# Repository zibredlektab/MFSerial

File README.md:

# MFSerial
Microforce Analog to Preston Serial converter

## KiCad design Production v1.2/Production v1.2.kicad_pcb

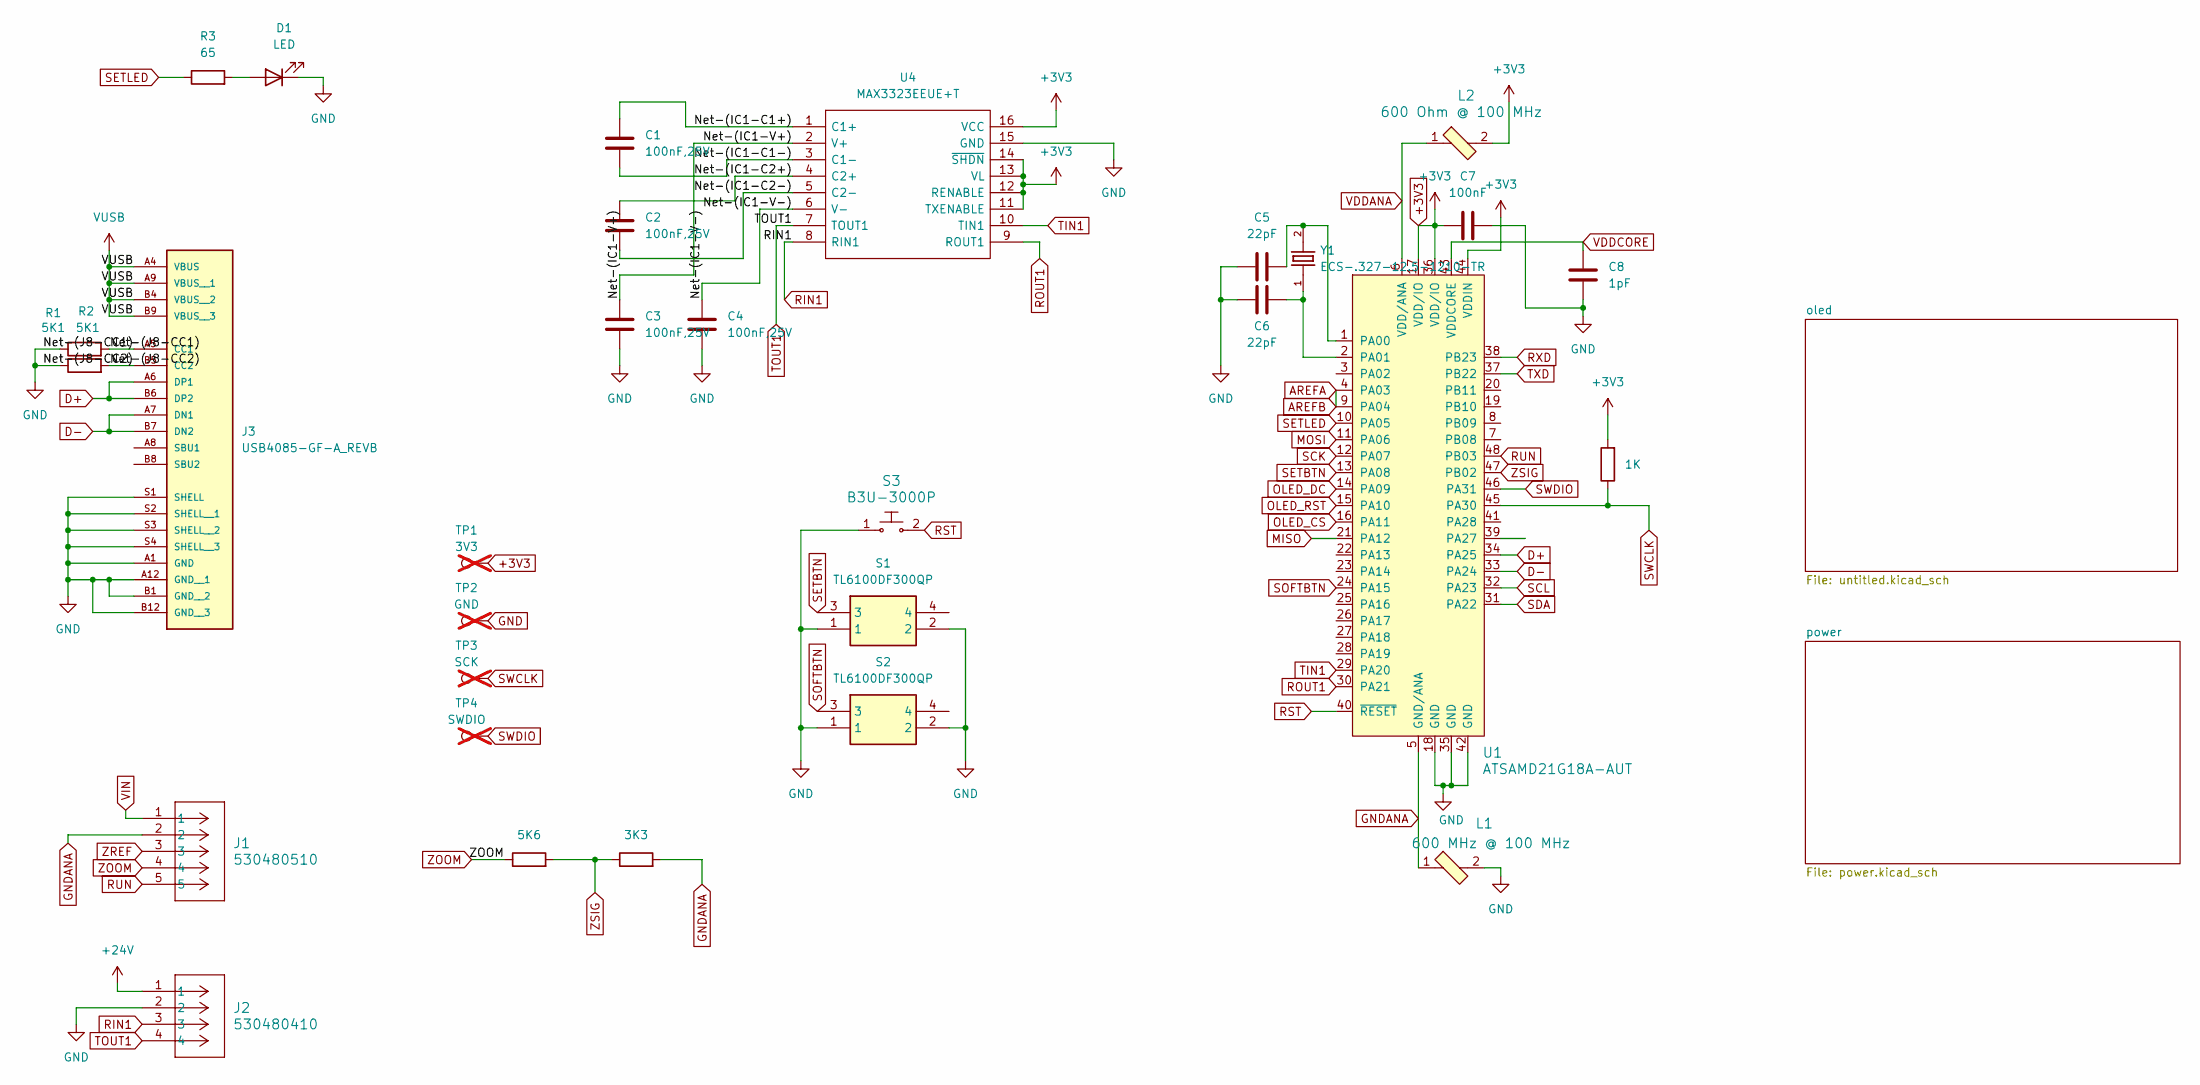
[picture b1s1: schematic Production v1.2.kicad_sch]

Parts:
C1, C2, C3, C4: 100nF,25V; C_0402_1005Metric; Part Number CL05B104KA5NNNC
C5, C6: 22pF; C_0402_1005Metric; Part Number CL05C220JB51PNC
C7: 100nF; C_0402_1005Metric; Part Number CL05B104KA5NNNC
C8: 1pF; C_0402_1005Metric; Part Number CL05C010CB5NNNC
D1: LED; LED_0805_2012Metric; Part Number B1701URO-20D000114U1930
J1: 530480510; Molex_PicoBlade_53048-0510_1x05_P1.25mm_Horizontal; Part Number 530480510
J2: 530480410; Molex_PicoBlade_53048-0410_1x04_P1.25mm_Horizontal; Part Number 530480410
J3: USB4085-GF-A_REVB; CONN16_USB4085-GF-A_GCT; Part Number USB4085-GF-A
L1: 600 MHz @ 100 MHz; 0603; Part Number 74269262601
L2: 600 Ohm @ 100 MHz; 0603; Part Number 74269262601
R1, R2: 5K1; R_0201_0603Metric; Part Number ERJ-1GNF5101C
R3: 65; R_0201_0603Metric; Part Number ERJ-1GNF64R9C
R4: 5K6; R_0402_1005Metric; Part Number ERA-2VRW5601X
R5: 3K3; R_0402_1005Metric; Part Number ERA-2VRW3301X
R6: 1K; R_0201_0603Metric; Part Number RC0201FR-071KL
S1, S2: TL6100DF300QP; TL6100DF160QP; Part Number TL6100DF300QP
S3: B3U-3000P; SW_SPST_B3U-3000P; Part Number B3U-3000P
TP1: 3V3; TestPoint_Pad_1.0x1.0mm; not fitted
TP2: GND; TestPoint_Pad_1.0x1.0mm; not fitted
TP3: SCK; TestPoint_Pad_1.0x1.0mm; not fitted
TP4: SWDIO; TestPoint_Pad_1.0x1.0mm; not fitted
U1: ATSAMD21G18A-AUT; TQFP-48_7x7mm_P0.5mm; Part Number ATSAMD21G18A-AUT
U4: MAX3323EEUE+T; TSSOP-16_4.4x5mm_P0.65mm; Part Number MAX3323EEUE+T
Y1: ECS-.327-12.5-1210-TR; XTAL_ECS-.327-12.5-1210-TR; Part Number ECS-.327-12.5-1210-TR

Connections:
+3V3: C7.1, L2.2, R6.2, TP1.1, U1.17 (VDD/IO), U1.36 (VDD/IO), U1.44 (VDDIN), U4.11 (TXENABLE), U4.12 (RENABLE), U4.13 (VL), U4.14 (~SHDN), U4.16 (VCC); also elsewhere on the board
+24V: J2.1; also elsewhere on the board
/Net-(IC1-C1+): C1.1, U4.1 (C1+)
/Net-(IC1-C1-): C1.2, U4.3 (C1-)
/Net-(IC1-C2+): C2.1, U4.4 (C2+)
/Net-(IC1-C2-): C2.2, U4.5 (C2-)
/Net-(IC1-V+): C3.1, U4.2 (V+)
/Net-(IC1-V-): C4.1, U4.6 (V-)
/Net-(J8-CC1): J3.A5 (CC1), R1.2
/Net-(J8-CC2): J3.B5 (CC2), R2.2
AREFA: U1.4 (PA03), U1.9 (PA04); also elsewhere on the board
D+: J3.A6 (DP1), J3.B6 (DP2), U1.34 (PA25)
D-: J3.A7 (DN1), J3.B7 (DN2), U1.33 (PA24)
GND: C3.2, C4.2, C5.1, C6.1, C7.2, C8.2, D1.1 (K), J2.2, J3.A1 (GND), J3.A12 (GND__1), J3.B1 (GND__2), J3.B12 (GND__3), J3.S1 (SHELL), J3.S2 (SHELL__1), J3.S3 (SHELL__2), J3.S4 (SHELL__3), L1.2, R1.1, R2.1, S1.1, S1.2, S2.1, S2.2, S3.1, TP2.1, U1.18 (GND), U1.35 (GND), U1.42 (GND), U4.15 (GND); also elsewhere on the board
GNDANA: J1.2, L1.1, R5.2, U1.5 (GND/ANA); also elsewhere on the board
MISO: U1.21 (PA12)
MOSI: U1.11 (PA06); also elsewhere on the board
unnamed: D1.2 (A), R3.2
unnamed: C5.2, U1.1 (PA00), Y1.2
unnamed: C6.2, U1.2 (PA01), Y1.1
OLED_CS: U1.16 (PA11); also elsewhere on the board
OLED_DC: U1.14 (PA09); also elsewhere on the board
OLED_RST: U1.15 (PA10); also elsewhere on the board
RIN1: J2.3, U4.8 (RIN1)
ROUT1: U1.30 (PA21), U4.9 (ROUT1)
RST: S3.2, U1.40 (~RESET)
RUN: J1.5, U1.48 (PB03)
RXD: U1.38 (PB23)
SCK: U1.12 (PA07); also elsewhere on the board
SCL: U1.32 (PA23)
SDA: U1.31 (PA22)
SETBTN: S1.3, U1.13 (PA08)
SETLED: R3.1, U1.10 (PA05)
SOFTBTN: S2.3, U1.24 (PA15)
SWCLK: R6.1, TP3.1, U1.45 (PA30)
SWDIO: TP4.1, U1.46 (PA31)
TIN1: U1.29 (PA20), U4.10 (TIN1)
TOUT1: J2.4, U4.7 (TOUT1)
TXD: U1.37 (PB22)
VDDANA: L2.1, U1.6 (VDD/ANA); also elsewhere on the board
VDDCORE: C8.1, U1.43 (VDDCORE)
VIN: J1.1; also elsewhere on the board
VUSB: J3.A4 (VBUS), J3.A9 (VBUS__1), J3.B4 (VBUS__2), J3.B9 (VBUS__3); also elsewhere on the board
ZOOM: J1.4, R4.1
ZREF: J1.3; also elsewhere on the board
ZSIG: R4.2, R5.1, U1.47 (PB02)

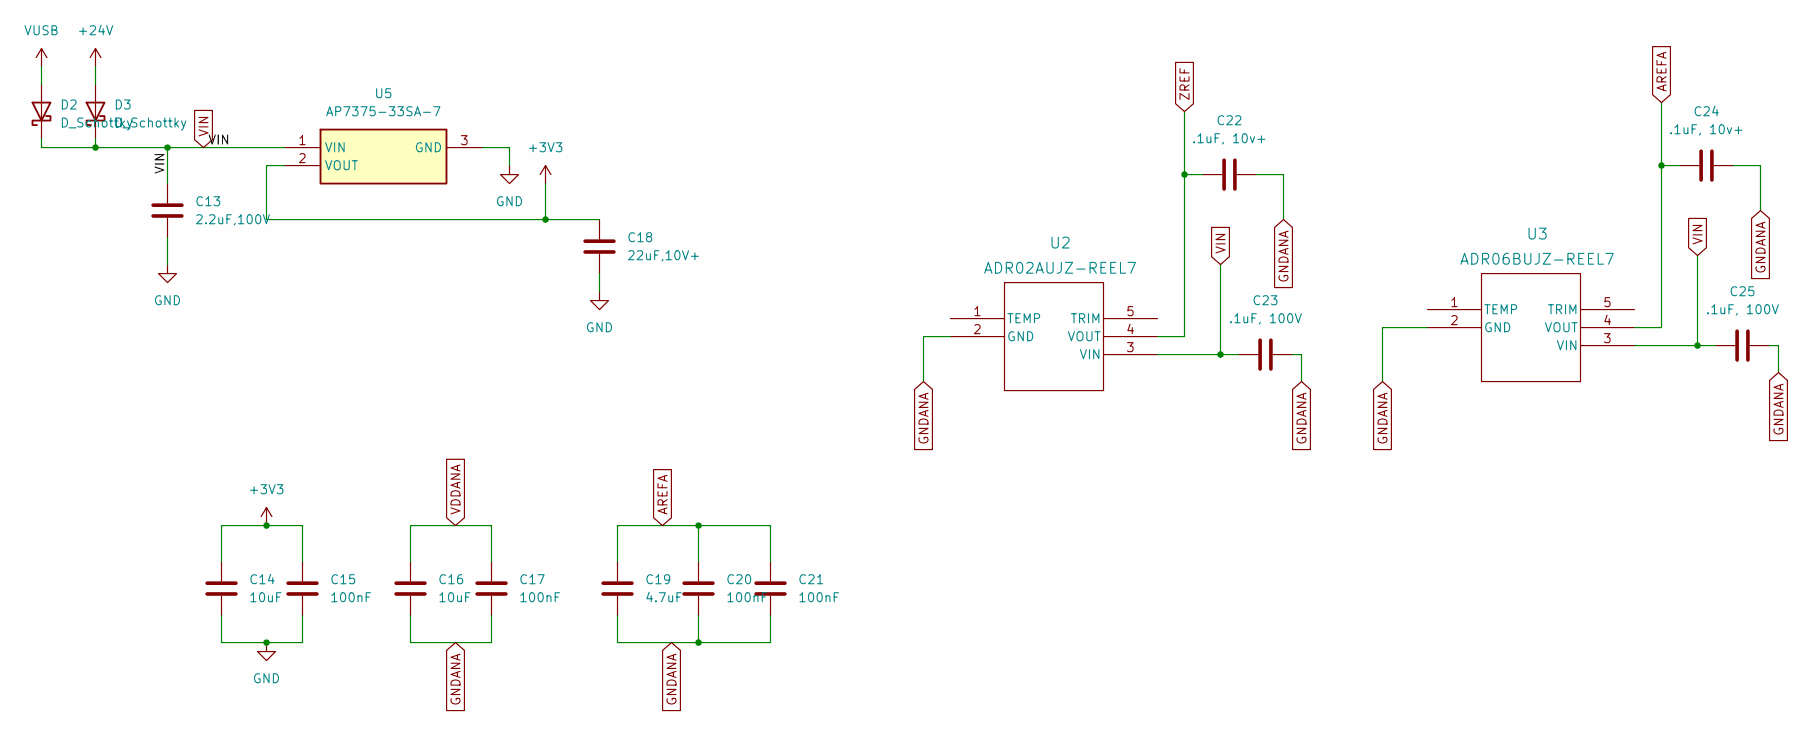
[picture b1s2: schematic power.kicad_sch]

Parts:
C13: 2.2uF,100V; C_0805_2012Metric; Part Number C2012X7R2A225K125AC
C14, C16: 10uF; C_0402_1005Metric; Part Number GRM155R61A106ME11D
C15, C17, C20, C21: 100nF; C_0402_1005Metric; Part Number CL05B104KA5NNNC
C18: 22uF,10V+; C_0402_1005Metric; Part Number GRM158R61A226ME15D
C19: 4.7uF; C_0402_1005Metric; Part Number CL05A475MP5NRNC
C22, C24: .1uF, 10v+; C_0402_1005Metric; Part Number CL05B104KP5NNNC
C23, C25: .1uF, 100V; C_0805_2012Metric; Part Number CL21B104KCFNNNE
D2, D3: D_Schottky; D_1206_3216Metric; Part Number SD1206S100S1R0
U2: ADR02AUJZ-REEL7; TSOT-23-5; Part Number ADR02AUJZ-REEL7
U3: ADR06BUJZ-REEL7; TSOT-23-5; Part Number ADR06BUJZ-REEL7
U5: AP7375-33SA-7; SOT96P240X110-3N; Part Number AP7375-33SA-7

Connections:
+3V3: C14.1, C15.1, C18.2, U5.2 (VOUT); also elsewhere on the board
+24V: D3.2 (A); also elsewhere on the board
AREFA: C19.1, C20.1, C21.1, C24.2, U3.4 (VOUT); also elsewhere on the board
GND: C13.1, C14.2, C15.2, C18.1, U5.3 (GND); also elsewhere on the board
GNDANA: C16.2, C17.2, C19.2, C20.2, C21.2, C22.1, C23.1, C24.1, C25.1, U2.2 (GND), U3.2 (GND); also elsewhere on the board
VDDANA: C16.1, C17.1; also elsewhere on the board
VIN: C13.2, C23.2, C25.2, D2.1 (K), D3.1 (K), U2.3 (VIN), U3.3 (VIN), U5.1 (VIN); also elsewhere on the board
VUSB: D2.2 (A); also elsewhere on the board
ZREF: C22.2, U2.4 (VOUT); also elsewhere on the board

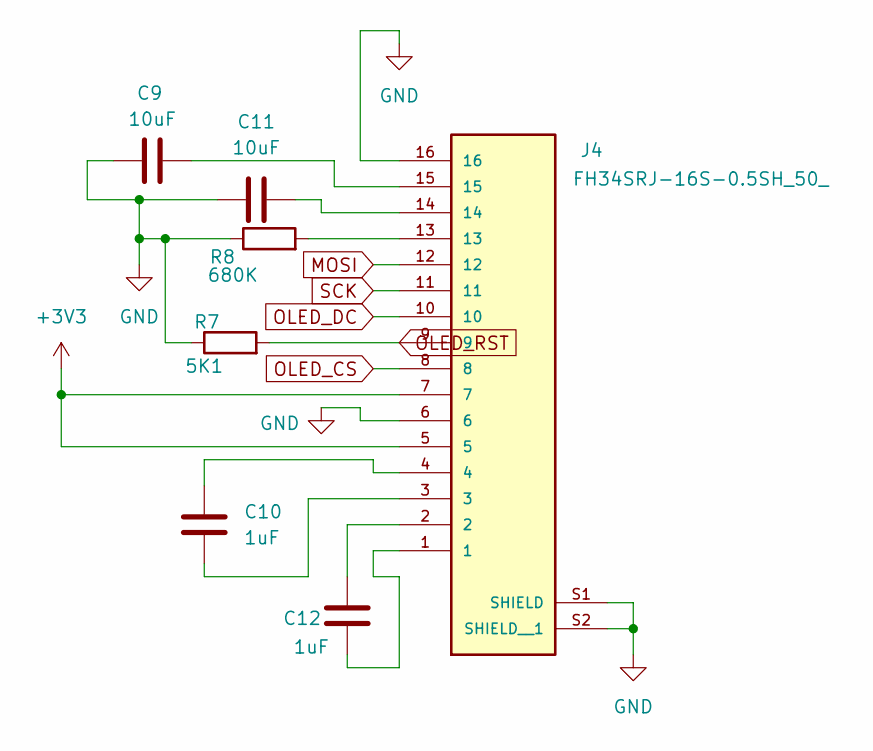
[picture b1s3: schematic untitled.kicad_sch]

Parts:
C9, C11: 10uF; C_0603_1608Metric; Part Number CL10A106KQ8NNNL
C10, C12: 1uF; C_0603_1608Metric; Part Number CL10B105KP8NNNC
J4: FH34SRJ-16S-0.5SH_50_; HRS_FH34SRJ-16S-0.5SH_50_; Part Number FH34SRJ-16S-0.5SH(50)
R7: 5K1; R_0201_0603Metric; Part Number ERJ-1GNF5101C
R8: 680K; R_0201_0603Metric; Part Number ERJ-1GNF6803C

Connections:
+3V3: J4.5, J4.7; also elsewhere on the board
GND: C9.1, C11.2, J4.6, J4.16, J4.S1 (SHIELD), J4.S2 (SHIELD__1), R7.1, R8.1; also elsewhere on the board
MOSI: J4.12; also elsewhere on the board
unnamed: C9.2, J4.15
unnamed: C10.1, J4.3
unnamed: C10.2, J4.4
unnamed: C11.1, J4.14
unnamed: C12.1, J4.1
unnamed: C12.2, J4.2
unnamed: J4.13, R8.2
OLED_CS: J4.8; also elsewhere on the board
OLED_DC: J4.10; also elsewhere on the board
OLED_RST: J4.9, R7.2; also elsewhere on the board
SCK: J4.11; also elsewhere on the board

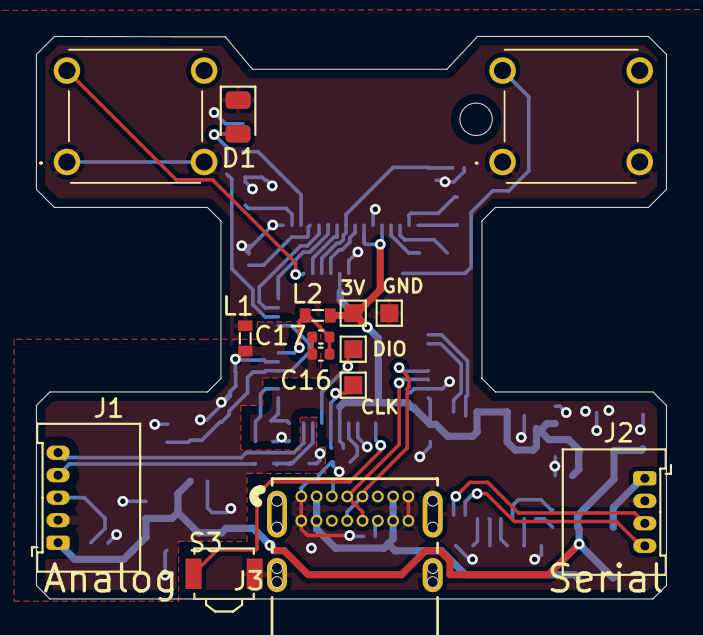
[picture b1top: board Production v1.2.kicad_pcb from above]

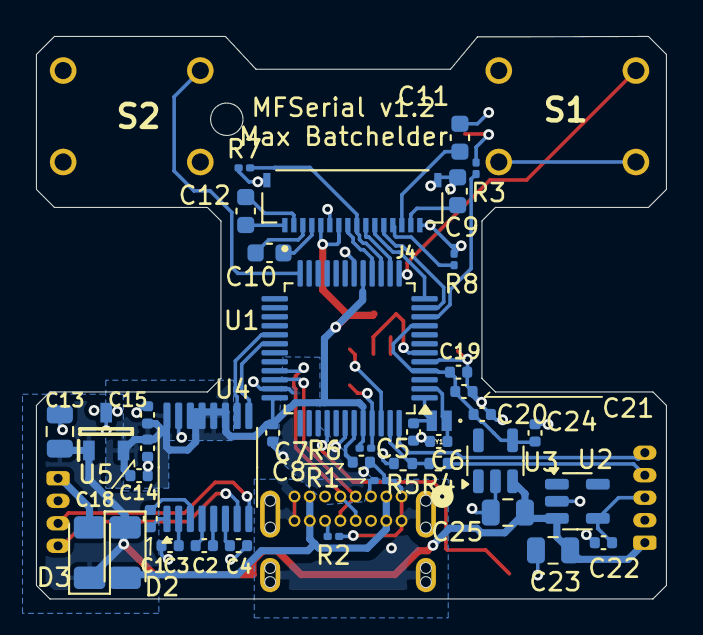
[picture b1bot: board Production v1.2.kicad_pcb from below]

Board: 2 copper layers, 35.0 x 31.2 mm, 55 parts (40 on the bottom side), 48 nets.

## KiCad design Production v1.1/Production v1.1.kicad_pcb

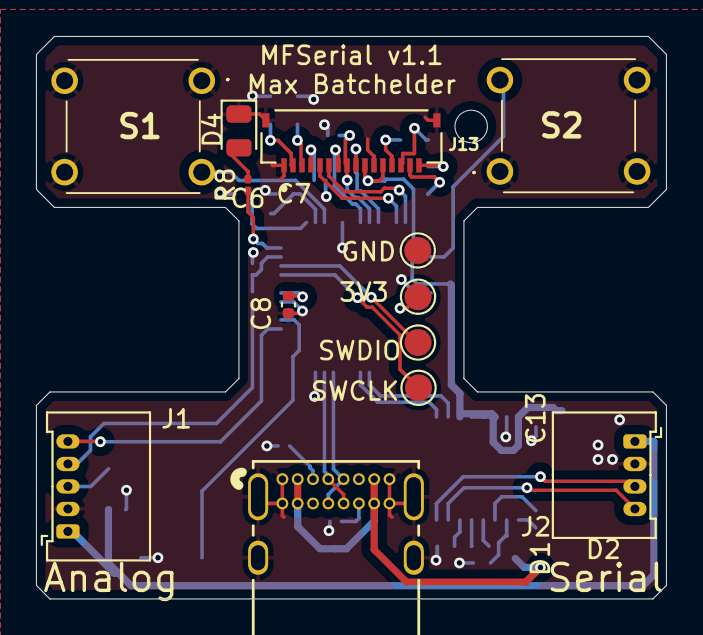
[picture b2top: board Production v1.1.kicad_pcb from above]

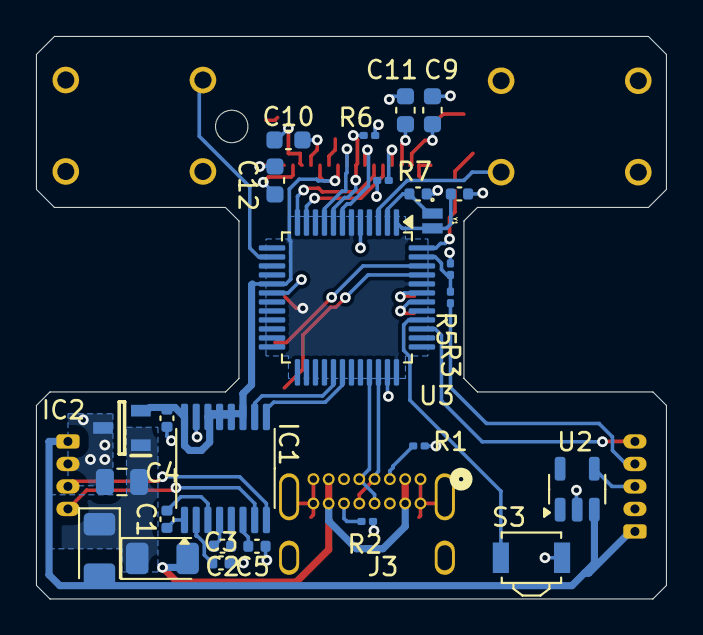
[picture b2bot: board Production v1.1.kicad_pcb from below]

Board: 2 copper layers, 35.0 x 31.2 mm, 39 parts (26 on the bottom side), 45 nets.

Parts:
3V3: TestPoint_Pad_D1.5mm
C1, C2, C3, C5: 100nF,24V+; C_0402_1005Metric
C4: 2.2uF,100V; C_0805_2012Metric
C6, C7: 22pF; C_0402_1005Metric
C8: 1pF; C_0402_1005Metric
C9, C11: 10uF; C_0603_1608Metric
C10, C12: 1uF; C_0603_1608Metric
C13: 22uF,10V+; C_0402_1005Metric
D1, D2: D_Schottky; D_1206_3216Metric
D4: LED; LED_0805_2012Metric
GND: TestPoint_Pad_D1.5mm
IC1: MAX3323EEUE+T; TSSOP-16_4.4x5mm_P0.65mm
IC2: AP7375-33SA-7; SOT96P240X110-3N
J1: 530480510; Molex_PicoBlade_53048-0510_1x05_P1.25mm_Horizontal
J2: 530480410; Molex_PicoBlade_53048-0410_1x04_P1.25mm_Horizontal
J3: USB4085-GF-A_REVB; CONN16_USB4085-GF-A_GCT
J13: FH34SRJ-16S-0.5SH_50_; HRS_FH34SRJ-16S-0.5SH_50_
R1, R2, R6: 5K1; R_0201_0603Metric
R3: 4K7; R_0201_0603Metric
R5: 3K3; R_0201_0603Metric
R7: 680K; R_0201_0603Metric
R8: 65; R_0201_0603Metric
S1, S2: TL6100DF300QP; TL6100DF160QP
S3: B3U-3000P; SW_SPST_B3U-3000P
SWCLK: TestPoint_Pad_D1.5mm
SWDIO: TestPoint_Pad_D1.5mm
U2: ADR02AUJZ-REEL7; TSOT-23-5
U3: ATSAMD21G18A-AUT; TQFP-48_7x7mm_P0.5mm
Y1: ECS-.327-12.5-1210-TR; XTAL_ECS-.327-12.5-1210-TR

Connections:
+3V3: 3V3.3, C13.2, IC1.11 (TXENABLE), IC1.12 (RENABLE), IC1.13 (VL), IC1.14 (~SHDN), IC1.16 (VCC), IC2.2 (VOUT), J13.10, J13.12, U3.6 (VDD/ANA), U3.17 (VDD/IO), U3.36 (VDD/IO), U3.44 (VDDIN)
+24V: D2.2 (A), J1.1, J2.1, U2.3 (VIN)
/Net-(IC1-C1+): C1.1, IC1.1 (C1+)
/Net-(IC1-C1-): C1.2, IC1.3 (C1-)
/Net-(IC1-C2+): C2.1, IC1.4 (C2+)
/Net-(IC1-C2-): C2.2, IC1.5 (C2-)
/Net-(IC1-V+): C3.1, IC1.2 (V+)
/Net-(IC1-V-): C5.1, IC1.6 (V-)
/Net-(J8-CC1): J3.A5 (CC1), R1.2
/Net-(J8-CC2): J3.B5 (CC2), R2.2
D+: J3.A6 (DP1), J3.B6 (DP2), U3.34 (PA25)
D-: J3.A7 (DN1), J3.B7 (DN2), U3.33 (PA24)
GND: C3.2, C4.1, C5.2, C6.1, C7.1, C8.2, C9.1, C11.2, C13.1, D4.1 (K), GND.4, IC1.15 (GND), IC2.3 (GND), J1.2, J2.2, J3.A1 (GND), J3.A12 (GND__1), J3.B1 (GND__2), J3.B12 (GND__3), J3.S1 (SHELL), J3.S2 (SHELL__1), J3.S3 (SHELL__2), J3.S4 (SHELL__3), J13.1, J13.11, J13.S1 (SHIELD), J13.S2 (SHIELD__1), R1.1, R2.1, R5.2, R6.1, R7.1, S1.1, S1.2, S1.4, S2.1, S2.2, S2.4, S3.1, U2.2 (GND), U3.5 (GND/ANA), U3.18 (GND), U3.35 (GND), U3.42 (GND)
MOSI: J13.5, U3.11 (PA06)
unnamed: C9.2, J13.2
unnamed: C10.1, J13.14
unnamed: C10.2, J13.13
unnamed: C11.1, J13.3
unnamed: C12.1, J13.16
unnamed: C12.2, J13.15
unnamed: D4.2 (A), R8.2
unnamed: J13.4, R7.2
unnamed: C6.2, U3.1 (PA00), Y1.2
unnamed: C7.2, U3.2 (PA01), Y1.1
unnamed: C8.1, U3.43 (VDDCORE)
OLED_CS: J13.9, U3.9 (PA04)
OLED_DC: J13.7, U3.7 (PB08)
OLED_RST: J13.8, R6.2, U3.8 (PB09)
RIN1: IC1.8 (RIN1), J2.3
ROUT1: IC1.9 (ROUT1), U3.30 (PA21)
RST: S3.2, U3.40 (~RESET)
RUN: J1.5, U3.39 (PA27)
SCK: J13.6, U3.12 (PA07)
SETBTN: S1.3, U3.3 (PA02)
SETLED: R8.1, U3.48 (PB03)
SOFTBTN: S2.3, U3.14 (PA09)
SWCLK: SWCLK.1, U3.45 (PA30)
SWDIO: SWDIO.3, U3.46 (PA31)
TIN1: IC1.10 (TIN1), U3.29 (PA20)
TOUT1: IC1.7 (TOUT1), J2.4
VIN: C4.2, D1.1 (K), D2.1 (K), IC2.1 (VIN)
VUSB: D1.2 (A), J3.A4 (VBUS), J3.A9 (VBUS__1), J3.B4 (VBUS__2), J3.B9 (VBUS__3)
ZOOM: J1.4, R3.1
ZREF: J1.3, U2.4 (VOUT)
ZSIG: R3.2, R5.1, U3.47 (PB02)

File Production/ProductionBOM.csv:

"Id";"Designator";"Footprint";"Quantity";"Designation";"Supplier and ref";
1;"C8";"C_0504_1310Metric";1;"1pF";;;
2;"D1,D2";"D_1206_3216Metric";2;"D_Schottky";;;
3;"C10,C12";"C_0504_1310Metric";2;"1uF";;;
4;"J1";"Molex_PicoBlade_53048-0510_1x05_P1.25mm_Horizontal";1;"530480510";;;
5;"C7,C6";"C_0504_1310Metric";2;"22pF";;;
6;"J3";"CONN16_USB4085-GF-A_GCT";1;"USB4085-GF-A_REVB";;;
7;"R1,R6,R2";"R_0603_1608Metric";3;"5K1";;;
8;"R8";"R_0603_1608Metric";1;"65";;;
9;"C5,C1,C3,C2";"C_0504_1310Metric";4;"100nF,24V+";;;
10;"U1";"TO-252-3_TabPin2";1;"BD33FC0FP-E2";;;
11;"SOFT1,SET1";"TS016673BK160D";2;"TS01-66-73-BK-160-D";;;
12;"J2";"Molex_PicoBlade_53048-0410_1x04_P1.25mm_Horizontal";1;"530480410";;;
13;"R7";"R_0603_1608Metric";1;"680K";;;
14;"IC1";"TSSOP-16_4.4x5mm_P0.65mm";1;"MAX3323EEPE+";;;
15;"R3";"R_0603_1608Metric";1;"4K7";;;
16;"J13";"HRS_FH34SRJ-16S-0.5SH_50_";1;"FH34SRJ-16S-0.5SH_50_";;;
17;"U3";"TQFP-48_7x7mm_P0.5mm";1;"ATSAMD21G18A-AUT";;;
18;"C11,C9";"C_0504_1310Metric";2;"10uF";;;
19;"U2";"TSOT-23-5";1;"ADR02AUJZ-REEL7";;;
20;"C13,C4";"C_0504_1310Metric";2;"20uF,60V+";;;
21;"Y1";"Crystal_SMD_3215-2Pin_3.2x1.5mm";1;"32.768, 12.5pF";;;
22;"D4";"LED_0805_2012Metric";1;"LED";;;
23;"R5";"R_0603_1608Metric";1;"3K3";;;
24;"RESET1";"SW_SPST_B3U-3000P";1;"B3U-1000P";;;

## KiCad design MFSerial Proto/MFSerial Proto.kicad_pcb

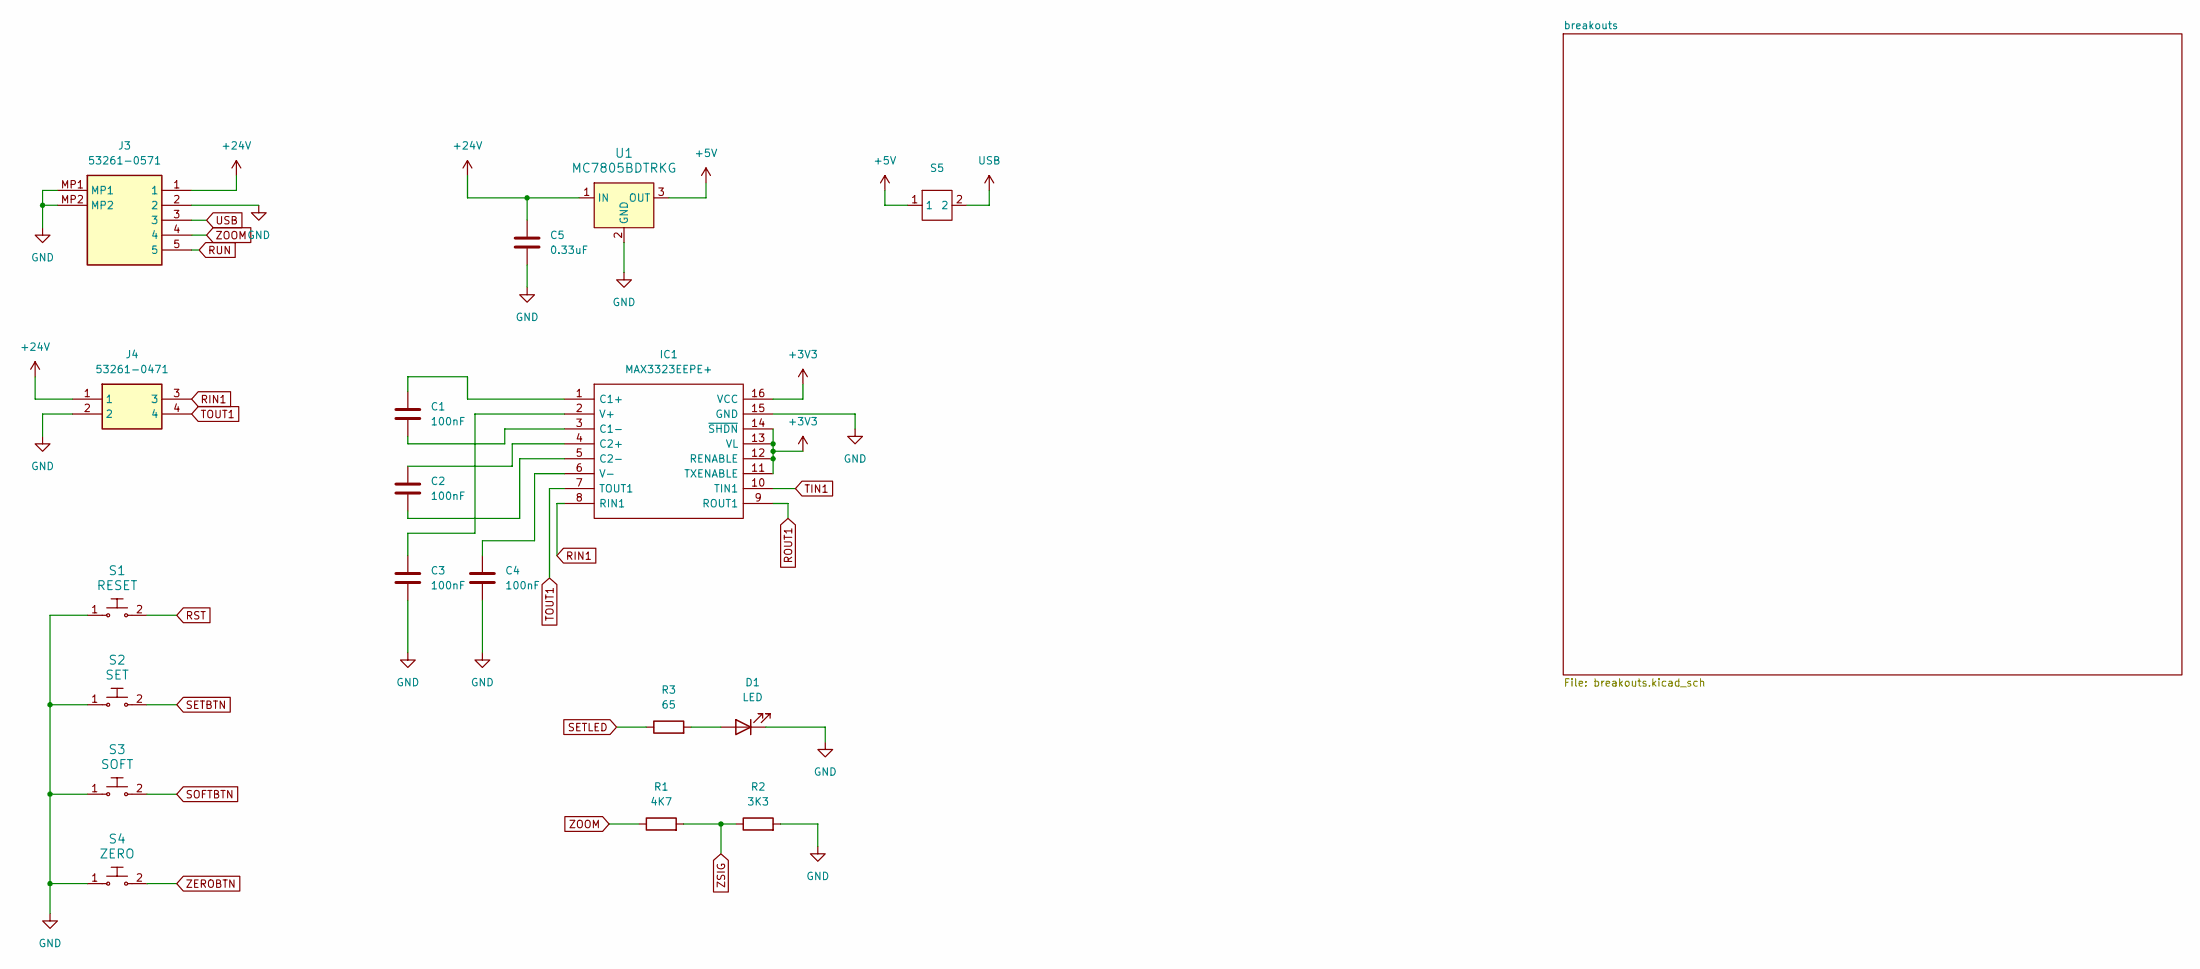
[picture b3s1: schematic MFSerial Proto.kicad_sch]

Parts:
C1, C2, C3, C4: 100nF; C_1812_4532Metric_Pad1.57x3.40mm_HandSolder
C5: 0.33uF; C_1812_4532Metric_Pad1.57x3.40mm_HandSolder
D1: LED; LED_5mm_Radial
IC1: MAX3323EEPE+; DIP794W56P254L1918H457Q16N; Mouser Part Number 700-MAX3323EEPE
J3: 53261-0571; 532610571TR250; Mouser Part Number 538-53261-0571
J4: 53261-0471; Mouser Part Number 538-53261-0471
R1: 4K7; R_1206_3216Metric_Pad1.30x1.75mm_HandSolder
R2: 3K3; R_1206_3216Metric_Pad1.30x1.75mm_HandSolder
R3: 65; R_1206_3216Metric_Pad1.30x1.75mm_HandSolder
S1: RESET; Switch_Tactile_SMD_B3U-1000P; MPN B3U-1000P
S2: SET; Switch_Tactile_SMD_B3U-1000P; MPN B3U-1000P
S3: SOFT; Switch_Tactile_SMD_B3U-1000P; MPN B3U-1000P
S4: ZERO; Switch_Tactile_SMD_B3U-1000P; MPN B3U-1000P
S5: DS04-254-1L-01
U1: MC7805BDTRKG; TO-220-3; MPN MC7805BDTRKG

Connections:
+3V3: IC1.11 (TXENABLE), IC1.12 (RENABLE), IC1.13 (VL), IC1.14 (~SHDN), IC1.16 (VCC); also elsewhere on the board
+5V: S5.1, U1.3 (OUT)
+24V: C5.2, J3.1, J4.1, U1.1 (IN); also elsewhere on the board
GND: C3.2, C4.2, C5.1, D1.1 (K), IC1.15 (GND), J3.2, J3.MP1, J3.MP2, J4.2, R2.2, S1.1, S2.1, S3.1, S4.1, U1.2 (GND); also elsewhere on the board
unnamed: D1.2 (A), R3.2
unnamed: C1.1, IC1.1 (C1+)
unnamed: C1.2, IC1.3 (C1-)
unnamed: C2.1, IC1.4 (C2+)
unnamed: C2.2, IC1.5 (C2-)
unnamed: C3.1, IC1.2 (V+)
unnamed: C4.1, IC1.6 (V-)
RIN1: IC1.8 (RIN1), J4.3; also elsewhere on the board
ROUT1: IC1.9 (ROUT1); also elsewhere on the board
RST: S1.2; also elsewhere on the board
RUN: J3.5; also elsewhere on the board
SETBTN: S2.2; also elsewhere on the board
SETLED: R3.1; also elsewhere on the board
SOFTBTN: S3.2; also elsewhere on the board
TIN1: IC1.10 (TIN1); also elsewhere on the board
TOUT1: IC1.7 (TOUT1), J4.4; also elsewhere on the board
USB: J3.3, S5.2; also elsewhere on the board
ZEROBTN: S4.2; also elsewhere on the board
ZOOM: J3.4, R1.1; also elsewhere on the board
ZSIG: R1.2, R2.1; also elsewhere on the board

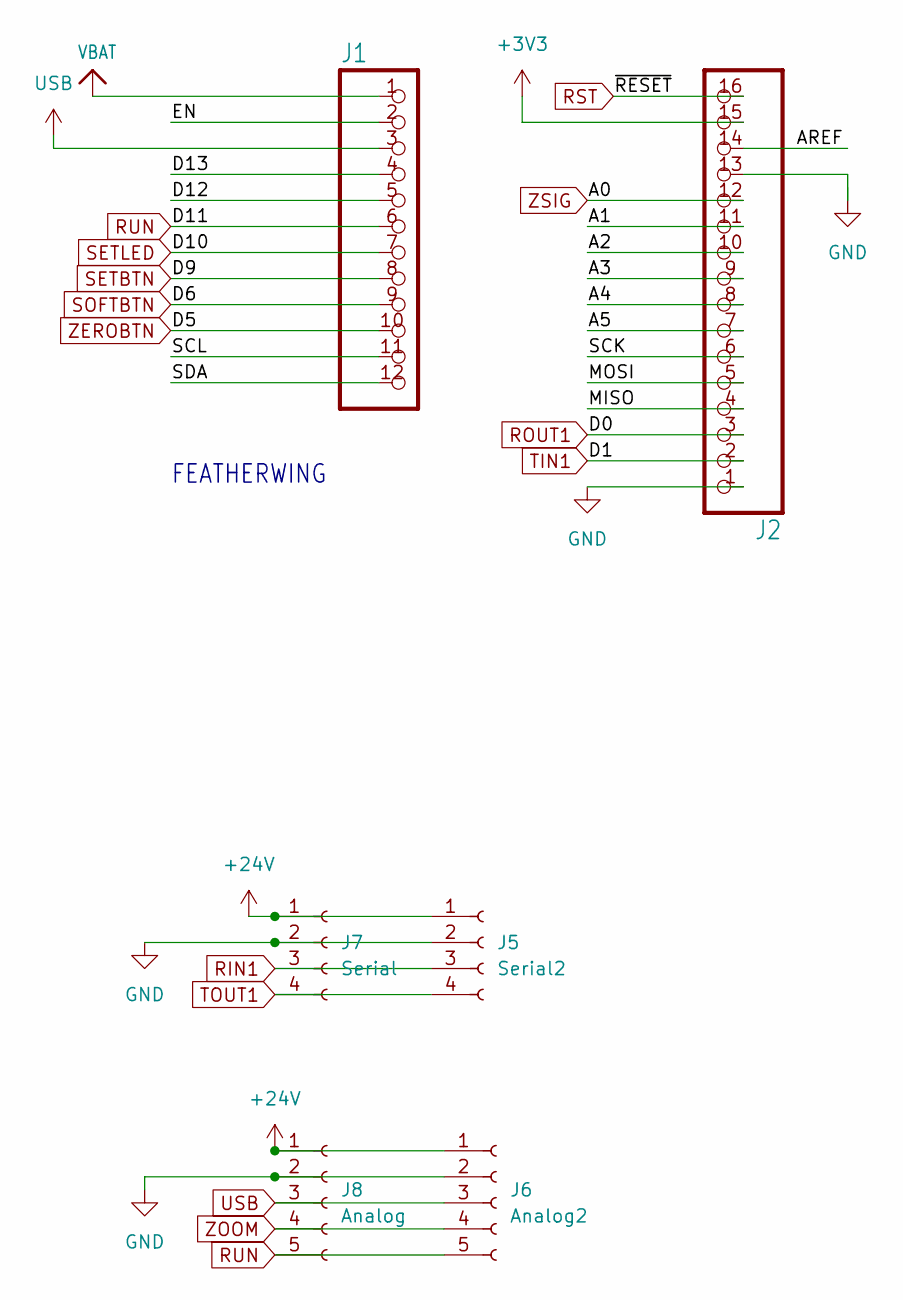
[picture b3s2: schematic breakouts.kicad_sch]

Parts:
J1: HEADER-1X12; PinHeader_1x12_P2.54mm_Vertical
J2: HEADER-1X16ROUND; PinHeader_1x16_P2.54mm_Vertical
J5: Serial2; PinSocket_1x04_P2.54mm_Vertical
J6: Analog2; PinSocket_1x05_P2.54mm_Vertical
J7: Serial; PinSocket_1x04_P2.54mm_Vertical
J8: Analog; PinSocket_1x05_P2.54mm_Vertical

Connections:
+3V3: J2.15; also elsewhere on the board
+24V: J5.1, J6.1, J7.1, J8.1; also elsewhere on the board
/breakouts/A1: J2.11
/breakouts/A2: J2.10
/breakouts/A3: J2.9
/breakouts/A4: J2.8
/breakouts/A5: J2.7
/breakouts/AREF: J2.14
/breakouts/D12: J1.5
/breakouts/D13: J1.4
/breakouts/EN: J1.2
/breakouts/MISO: J2.4
/breakouts/MOSI: J2.5
/breakouts/SCK: J2.6
/breakouts/SCL: J1.11
/breakouts/SDA: J1.12
GND: J2.1, J2.13, J5.2, J6.2, J7.2, J8.2; also elsewhere on the board
RIN1: J5.3, J7.3; also elsewhere on the board
ROUT1: J2.3; also elsewhere on the board
RST: J2.16; also elsewhere on the board
RUN: J1.6, J6.5, J8.5; also elsewhere on the board
SETBTN: J1.8; also elsewhere on the board
SETLED: J1.7; also elsewhere on the board
SOFTBTN: J1.9; also elsewhere on the board
TIN1: J2.2; also elsewhere on the board
TOUT1: J5.4, J7.4; also elsewhere on the board
USB: J1.3, J6.3, J8.3; also elsewhere on the board
VBAT: J1.1
ZEROBTN: J1.10; also elsewhere on the board
ZOOM: J6.4, J8.4; also elsewhere on the board
ZSIG: J2.12; also elsewhere on the board

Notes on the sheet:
FEATHERWING

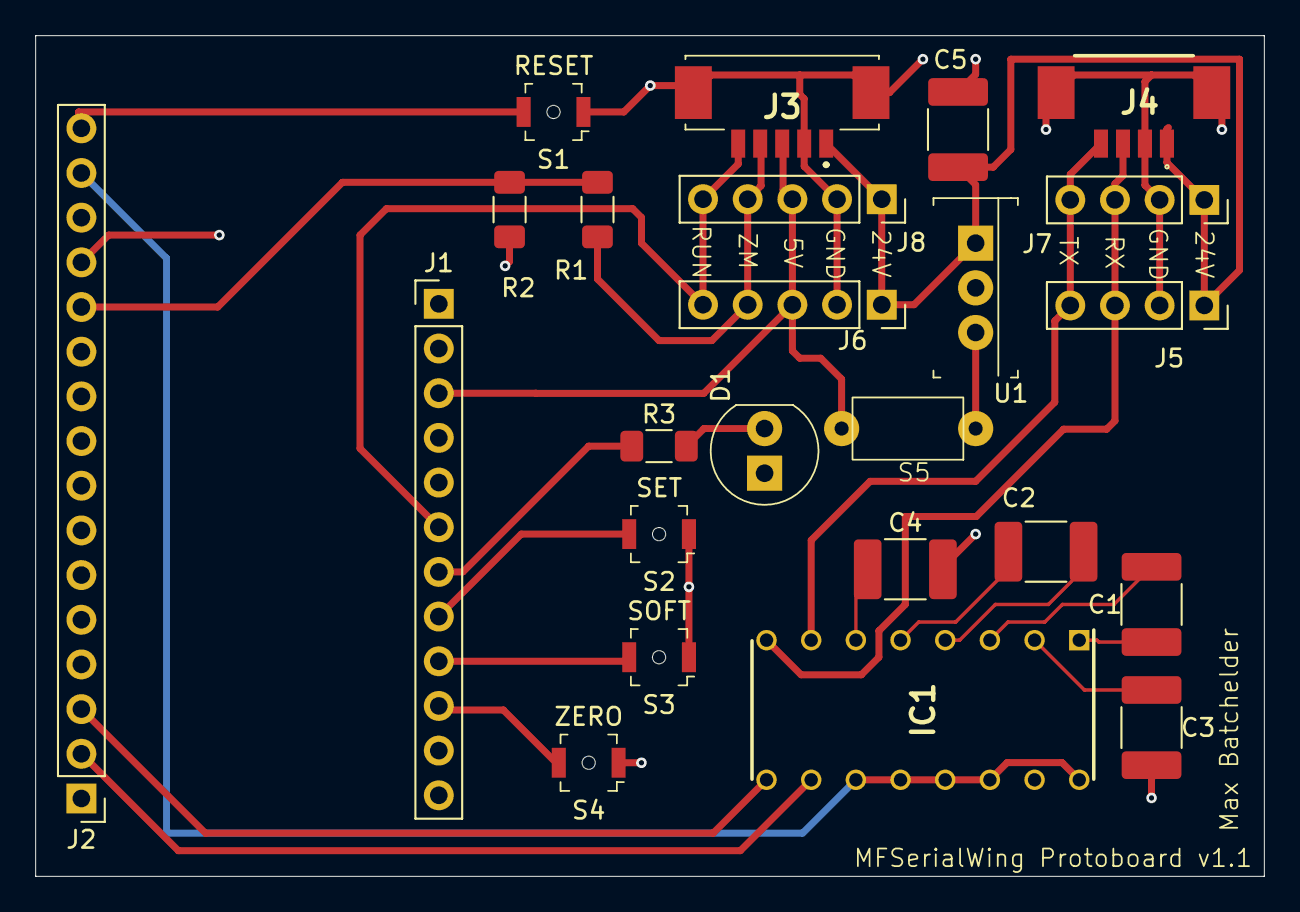
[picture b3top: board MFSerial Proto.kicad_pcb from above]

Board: 2 copper layers, 69.9 x 47.8 mm, 24 parts (0 on the bottom side), 24 nets.

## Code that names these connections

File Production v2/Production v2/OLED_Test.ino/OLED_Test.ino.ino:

#include <SPI.h>
#include <Wire.h>
#include <Adafruit_GFX.h>
#include <Adafruit_SH110X.h>

#define OLED_DC 2
#define OLED_CS 5
#define OLED_RST 4

Adafruit_SH1106G display = Adafruit_SH1106G(128, 64, &SPI, OLED_DC, OLED_RST, OLED_CS);

// OLED FeatherWing buttons map to different pins depending on board:
#if defined(ESP8266)
  #define BUTTON_A  0
  #define BUTTON_B 16
  #define BUTTON_C  2
#elif defined(ESP32) && !defined(ARDUINO_ADAFRUIT_FEATHER_ESP32S2)
  #define BUTTON_A 15
  #define BUTTON_B 32
  #define BUTTON_C 14
#elif defined(ARDUINO_STM32_FEATHER)
  #define BUTTON_A PA15
  #define BUTTON_B PC7
  #define BUTTON_C PC5
#elif defined(TEENSYDUINO)
  #define BUTTON_A  4
  #define BUTTON_B  3
  #define BUTTON_C  8
#elif defined(ARDUINO_NRF52832_FEATHER)
  #define BUTTON_A 31
  #define BUTTON_B 30
  #define BUTTON_C 27
#else // 32u4, M0, M4, nrf52840, esp32-s2 and 328p
  #define BUTTON_A  9
  #define BUTTON_B  6
  #define BUTTON_C  5
#endif

void setup() {
  Serial.begin(115200);
  while(!Serial){}
  Serial.println("128x64 OLED FeatherWing test");
  delay(250); // wait for the OLED to power up
  if (display.begin(0, true)) { // Address 0x3C default

    Serial.println("OLED begun");
  } else {
    Serial.println("OLED failed to initialize");
  }

  // Show image buffer on the display hardware.
  // Since the buffer is intialized with an Adafruit splashscreen
  // internally, this will display the splashscreen.
  display.display();
  delay(1000);

  // Clear the buffer.
  display.clearDisplay();
  display.display();

  display.setRotation(1);
 /* Serial.println("Button test");

  pinMode(BUTTON_A, INPUT_PULLUP);
  pinMode(BUTTON_B, INPUT_PULLUP);
  pinMode(BUTTON_C, INPUT_PULLUP);*/

  // text display tests
  display.setTextSize(1);
  display.setTextColor(SH110X_WHITE);
  display.setCursor(0,0);
  display.print("Connecting to SSID\n'adafruit':");
  display.print("connected!");
  display.println("IP: 10.0.1.23");
  display.println("Sending val #0");
  display.display(); // actually display all of the above
}

void loop() {
  if(!digitalRead(BUTTON_A)) display.print("A");
  if(!digitalRead(BUTTON_B)) display.print("B");
  if(!digitalRead(BUTTON_C)) display.print("C");
  delay(10);
  yield();
  display.display();
}

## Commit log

2024-05-30 Initial Commit
    MFSerialProto (featherwing design) and MFSerial Standalone (standalone prototype board), as ordered for manufacture
2024-05-30 Added f3d file for MFSerialProto case
2024-05-31 ignore Mac stuff
2024-07-26 Started work on production board v1
2024-07-28 Solid layout, could be better
2024-07-28 Combined TXLED and SETLED
2024-07-29 I layout
2024-08-01 Changing power regulator
2024-08-09 Pretty solid I redesign
    Rotated mcu and reassigned pins for better layout, swapped ldo
2024-08-09 more of previous
2024-08-15 Unsure of what this change is, sorry
2024-08-15 Reloaded footprints & models after switching back to mac
2024-08-16 Tweaked some cap sizes & layout accordingly
2024-08-19 v1, as submitted for production
2024-08-20 Updated BOM to include part numbers
2024-09-14 Updated oled test arduino files
2024-09-25 Create LICENSE
2024-10-22 Some minor board tweaks
2024-11-12 Solid v1.1 attempt, but going to start over
2024-11-15 Better v1.1, but I can do better
2024-11-16 Components are all moved to the bottom layer, top is ground
2024-11-18 Solid v1.1, but I want to change how the oled is mounted.
2024-11-19 v1.1 sent for assembly
2024-11-21 Updated v1.1 and re-ordered
    One net was not connected
2024-11-22 Resubmitted again, no more vias in pads
2025-01-05 added some unnecessary files to gitignore
2025-01-05 and removed some old design files
2025-01-05 Added v1.1 uf2 config files
2025-03-14 Started v1.2
2025-03-15 1.2 routed
2025-03-15 v1.2 checked & labeled
    flipped fpc connector to underside, for better ribbon routing.
2025-03-24 Updated some fields
2025-05-16 Final tweaks for production v1.2, as manufactured
2025-10-07 updated uf2 board config
2025-10-07 v1.2 UF2 bootloader
2025-10-07 more uf2 tweaks
